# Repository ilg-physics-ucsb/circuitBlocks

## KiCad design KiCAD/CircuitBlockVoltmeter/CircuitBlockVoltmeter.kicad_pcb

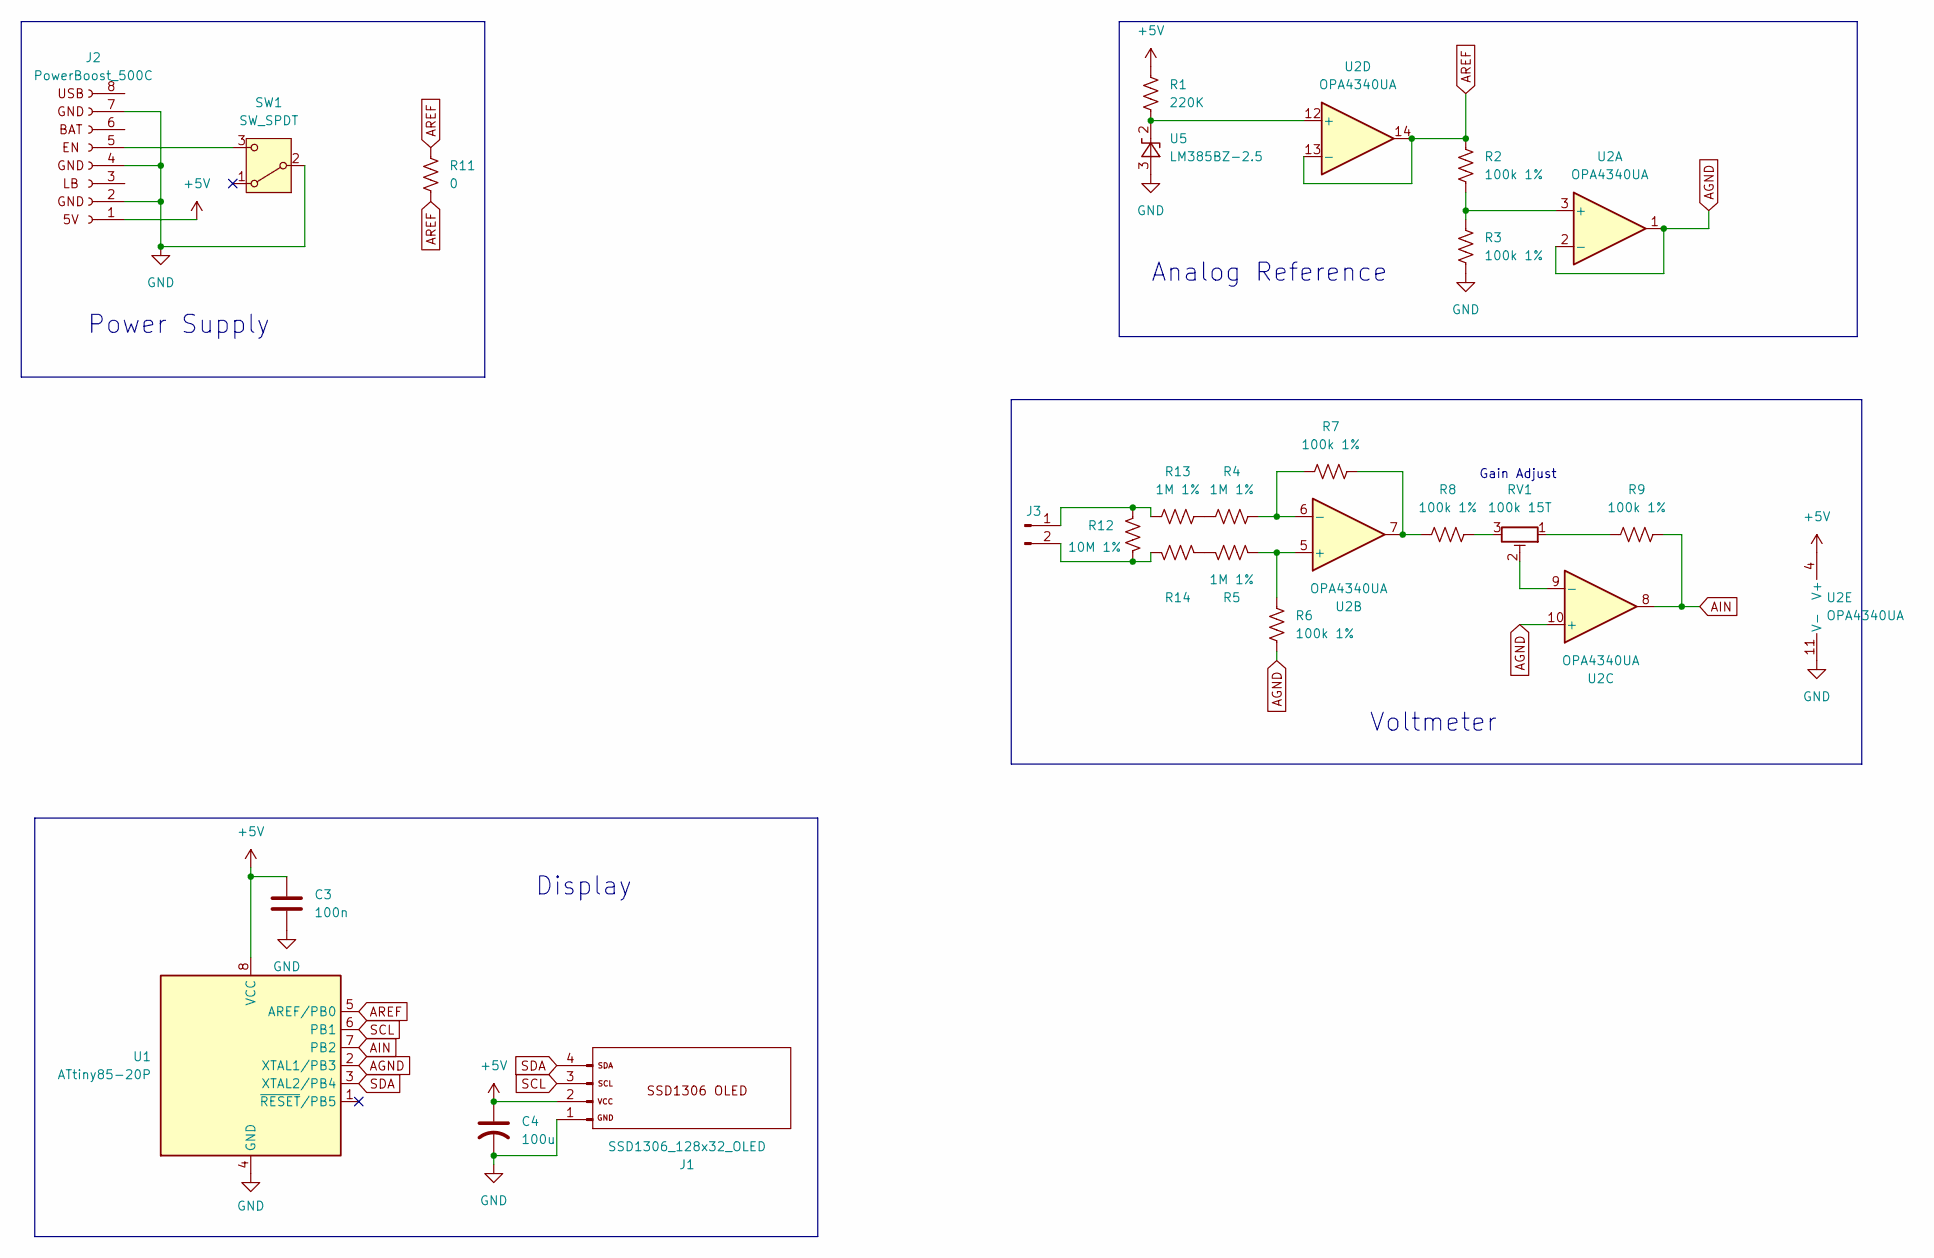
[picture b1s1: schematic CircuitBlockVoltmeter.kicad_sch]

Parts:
C3: 100n; C_Disc_D7.0mm_W2.5mm_P5.00mm
C4: 100u; C_Radial_D6.3mm_H7.0mm_P2.50mm
J1: SSD1306_128x32_OLED
J2: PowerBoost_500C; PowerBoost 500C
J3: Conn_01x02_Pin; PinHeader_1x02_P2.54mm_Vertical
R1: 220K; R_Axial_DIN0207_L6.3mm_D2.5mm_P10.16mm_Horizontal
R2, R6: 100k 1%; R_Axial_DIN0207_L6.3mm_D2.5mm_P10.16mm_Horizontal
R3, R8: 100k 1%; R_Axial_DIN0207_L6.3mm_D2.5mm_P7.62mm_Horizontal
R4, R5: 1M 1%; R_Axial_DIN0207_L6.3mm_D2.5mm_P10.16mm_Horizontal
R7, R9: 100k 1%; R_Axial_DIN0207_L6.3mm_D2.5mm_P2.54mm_Vertical
R11: 0; R_Axial_DIN0207_L6.3mm_D2.5mm_P7.62mm_Horizontal
R12: 10M 1%; R_Axial_DIN0207_L6.3mm_D2.5mm_P7.62mm_Horizontal
R13, R14: 1M 1%; R_Axial_DIN0207_L6.3mm_D2.5mm_P7.62mm_Horizontal
RV1: 100k 15T; Potentiometer_Bourns_3296W_Vertical
SW1: SW_SPDT; SW_Slide_SPDT_Angled_CK_OS102011MA1Q
U1: ATtiny85-20P; DIP-8_W7.62mm
U2: OPA4340UA; SOIC-14_3.9x8.7mm_P1.27mm
U5: LM385BZ-2.5; TO-92_Inline

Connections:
+5V: C3.1, C4.1, J1.2 (VCC), J2.1 (5V), R1.1, U1.8 (VCC), U2.4 (V+)
AGND: R6.2, U1.2 (XTAL1/PB3), U2.1, U2.2 (-), U2.10 (+)
AIN: R9.2, U1.7 (PB2), U2.8
AREF: R2.1, R11.1, R11.2, U1.5 (AREF/PB0), U2.13 (-), U2.14
GND: C3.2, C4.2, J1.1 (GND), J2.2 (GND), J2.4 (GND), J2.7 (GND), R3.2, SW1.2 (B), U1.4 (GND), U2.11 (V-), U5.3 (A)
unnamed: J2.5 (EN), SW1.3 (C)
unnamed: J3.1, R12.1, R13.1
unnamed: J3.2, R12.2, R14.1
unnamed: R7.2, R8.2, U2.7
unnamed: R8.1, RV1.3
unnamed: R9.1, RV1.1
unnamed: R4.1, R13.2
unnamed: R5.1, R14.2
unnamed: R2.2, R3.1, U2.3 (+)
unnamed: R5.2, R6.1, U2.5 (+)
unnamed: R4.2, R7.1, U2.6 (-)
unnamed: RV1.2, U2.9 (-)
unnamed: R1.2, U2.12 (+), U5.2 (K)
SCL: J1.3 (SCL), U1.6 (PB1)
SDA: J1.4 (SDA), U1.3 (XTAL2/PB4)

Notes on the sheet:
Power Supply
Analog Reference
Voltmeter
Gain Adjust
Display

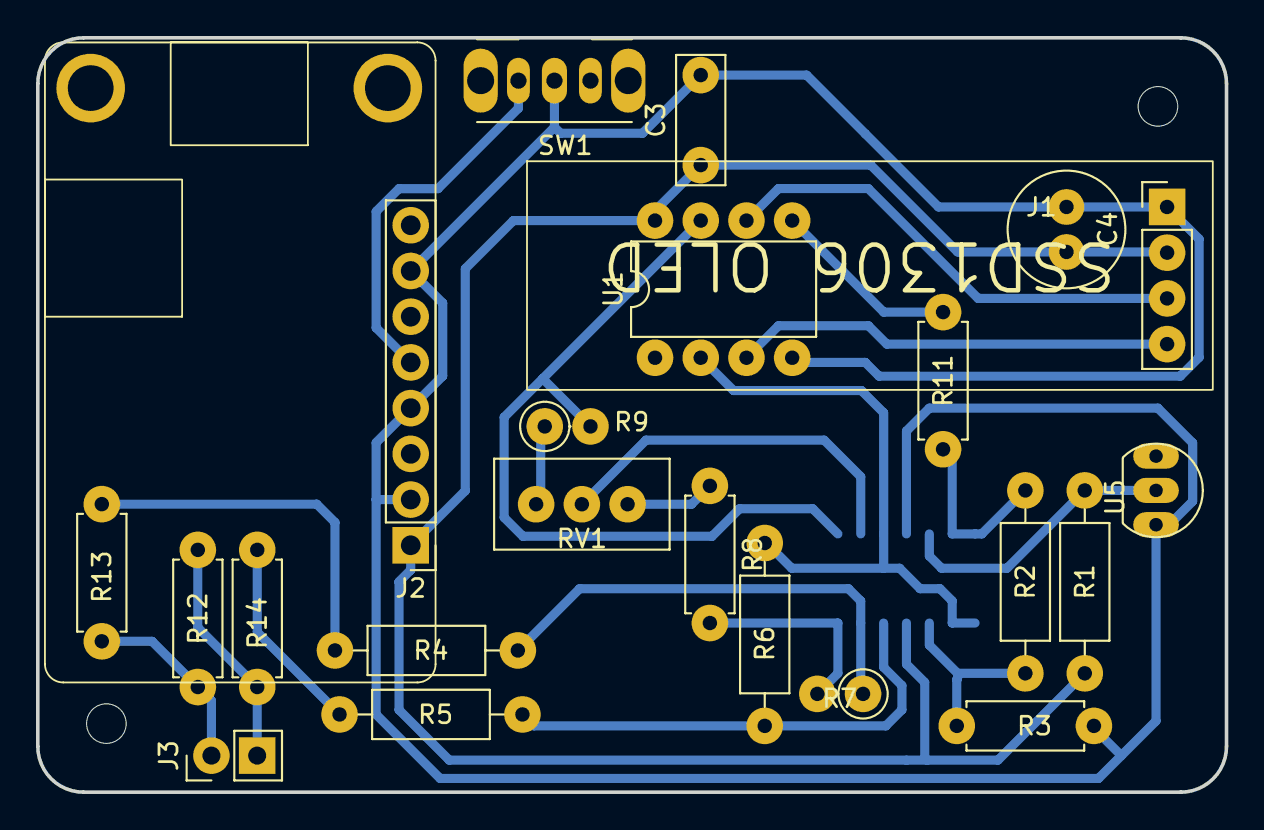
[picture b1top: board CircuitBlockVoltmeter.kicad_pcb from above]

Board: 2 copper layers, 66.0 x 41.9 mm, 23 parts (1 on the bottom side), 20 nets.

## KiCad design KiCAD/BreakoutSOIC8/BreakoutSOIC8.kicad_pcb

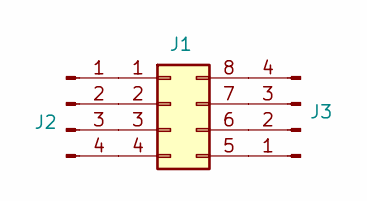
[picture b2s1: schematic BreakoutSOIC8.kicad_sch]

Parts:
J1: Conn_02x04_Counter_Clockwise; SOIC-8_3.9x4.9mm_P1.27mm
J2, J3: Conn_01x04_Pin; PinHeader_1x04_P2.54mm_Vertical

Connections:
unnamed: J1.1, J2.1
unnamed: J1.2, J2.2
unnamed: J1.3, J2.3
unnamed: J1.4, J2.4
unnamed: J1.5, J3.1
unnamed: J1.6, J3.2
unnamed: J1.7, J3.3
unnamed: J1.8, J3.4

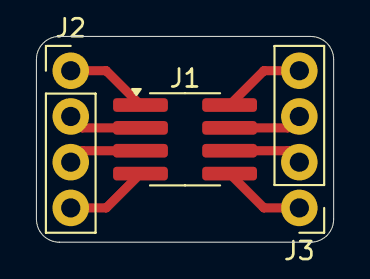
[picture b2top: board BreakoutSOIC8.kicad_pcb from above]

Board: 2 copper layers, 16.5 x 11.4 mm, 3 parts (0 on the bottom side), 8 nets.

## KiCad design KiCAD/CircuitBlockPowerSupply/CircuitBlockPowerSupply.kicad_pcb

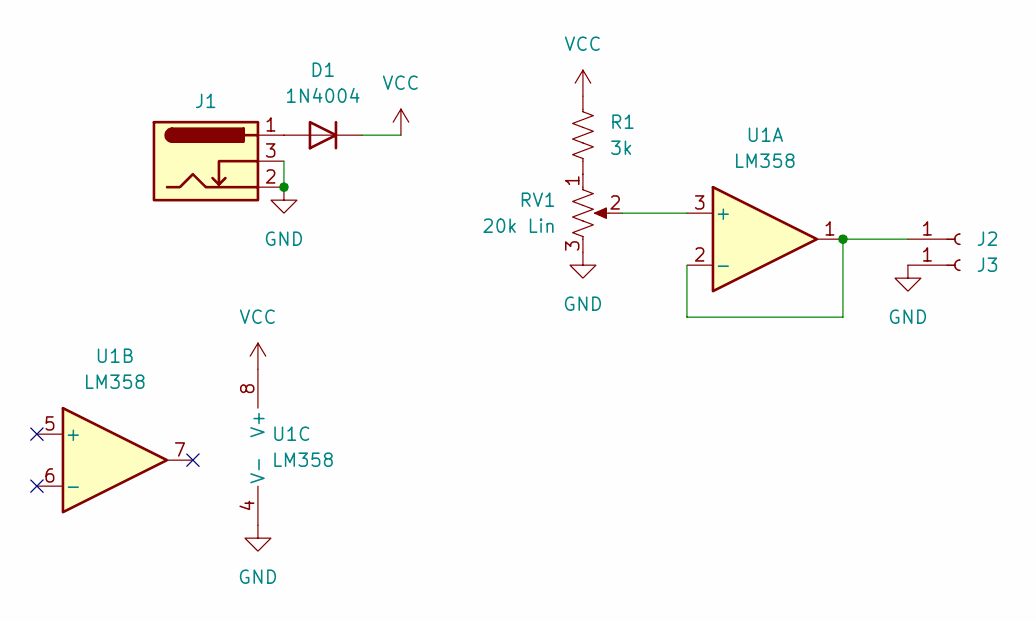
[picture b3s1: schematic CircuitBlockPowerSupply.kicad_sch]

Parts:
D1: 1N4004; D_DO-41_SOD81_P10.16mm_Horizontal
J1: Barrel_Jack_Switch; BarrelJack_Horizontal
J2, J3: Conn_01x01_Socket; PinHeader_1x01_P1.00mm_Vertical
R1: 3k; R_Axial_DIN0207_L6.3mm_D2.5mm_P10.16mm_Horizontal
RV1: 20k Lin; PTV09A4020FB103
U1: LM358; DIP-8_W7.62mm_LongPads

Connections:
GND: J1.2, J1.3, J3.1, RV1.3, U1.4 (V-)
unnamed: D1.2 (A), J1.1
unnamed: J2.1, U1.1, U1.2 (-)
unnamed: R1.2, RV1.1
unnamed: RV1.2, U1.3 (+)
VCC: D1.1 (K), R1.1, U1.8 (V+)

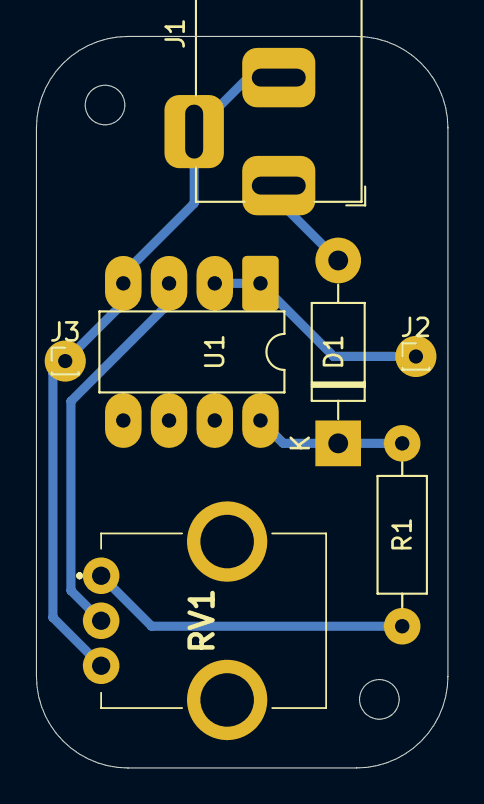
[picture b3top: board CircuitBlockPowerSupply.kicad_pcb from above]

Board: 2 copper layers, 22.9 x 40.6 mm, 7 parts (0 on the bottom side), 6 nets.

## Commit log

2025-06-05 Add all existing CAD files
2025-06-13 Edit CAD
2025-06-17 Add volt/am meter CAD
